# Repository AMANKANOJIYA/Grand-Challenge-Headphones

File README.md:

# Grand-Challenge-Headphones
The main objective of this grand challenge was to energize young minds and develop indigenous innovative commercially viable 
product designs which can be up- scaled further under a Centre of Excellence being setup by Centre for Development of Advanced 
Computing (CDAC).
# P-007: To design a low-cost Bluetooth or a USB headset
A headset is a device that provides a two-way connection to the user's cell phone via Bluetooth.
Expected features are touch control, noise cancellation, low battery consumption.

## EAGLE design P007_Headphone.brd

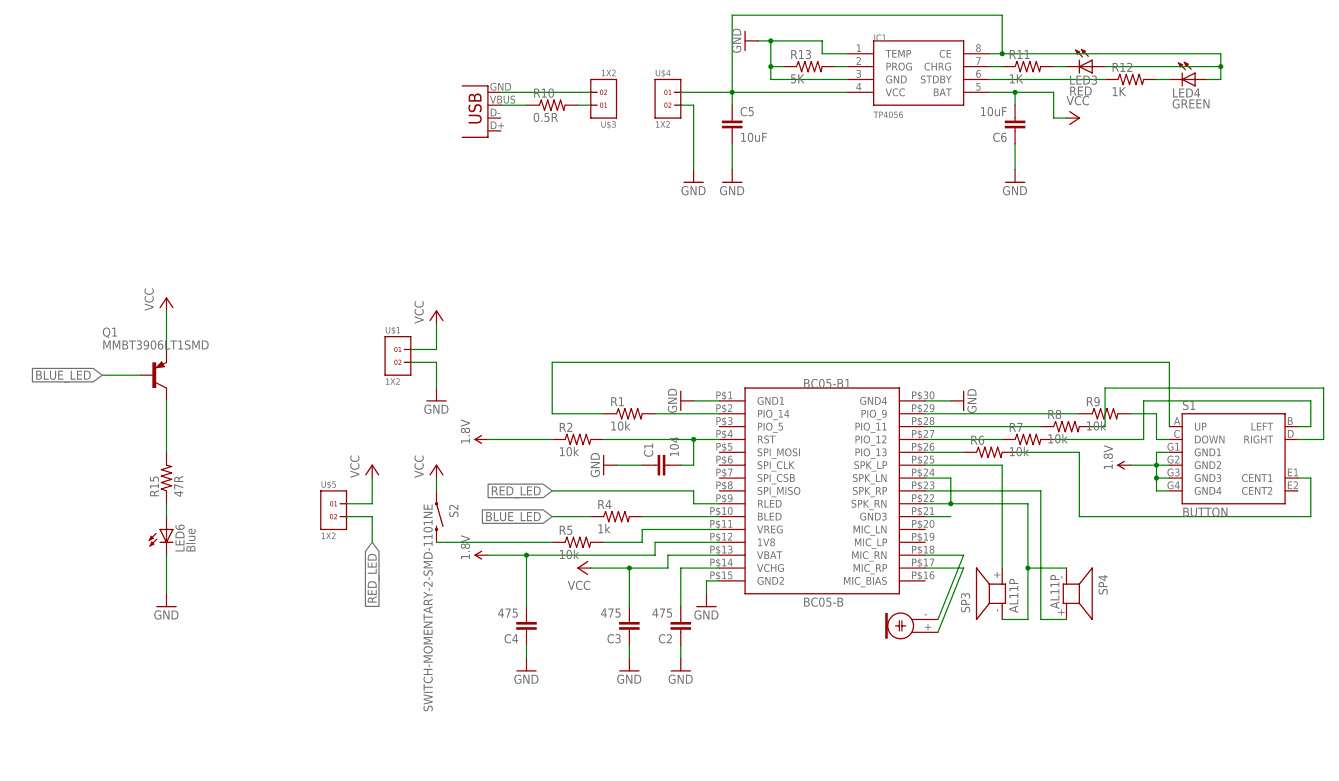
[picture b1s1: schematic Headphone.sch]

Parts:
BC05-B1: BC05-B
C1: 104; C0603K
C2, C3, C4: 475; C0603K
C5, C6: 10uF; C0805K
IC1: TP4056; SOP-8
LED3: RED; CHIP-LED0805
LED4: GREEN; CHIP-LED0805
LED6: Blue; CHIP-LED0805
M1: ELECTRET_MICROPHON-TOM-1545P-R; TOM-1545P-R
Q1: MMBT3906LT1SMD; SOT23-BEC
R1, R2, R5, R6, R7, R8, R9: 10k; R0603
R4: 1k; R0603
R10: 0.5R; M0805
R11, R12: 1K; R0603
R13: 5K; R0603
R15: 47R; R0603
S1: BUTTON
S2: SWITCH-MOMENTARY-2-SMD-1101NE; TACTILE-SWITCH-1101NE
SP3, SP4: AL11P
U$1, U$3, U$4, U$5: 1X2
X1: USB-MICROB

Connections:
1.8V: BC05-B1.P$12 (1V8), C4.2, R2.1, S1.G1 (GND1), S1.G2 (GND2), S1.G3 (GND3), S1.G4 (GND4)
BLUE_LED: Q1.B, R4.1
GND: BC05-B1.P$1 (GND1), BC05-B1.P$15 (GND2), BC05-B1.P$30 (GND4), C1.1, C2.1, C3.1, C4.1, C5.2, C6.1, IC1.1 (TEMP), IC1.3 (GND), LED6.C, R13.1, U$1.2, U$4.2
unnamed: BC05-B1.P$2 (PIO_14), R1.2
unnamed: BC05-B1.P$4 (RST), C1.2, R2.2
unnamed: BC05-B1.P$11 (VREG), R5.2
unnamed: BC05-B1.P$10 (BLED), R4.2
unnamed: BC05-B1.P$17 (MIC_RP), M1.+ (1)
unnamed: BC05-B1.P$18 (MIC_RN), M1.- (2)
unnamed: BC05-B1.P$25 (SPK_LP), SP3.+ (2)
unnamed: BC05-B1.P$29 (PIO_9), R9.1
unnamed: BC05-B1.P$28 (PIO_11), R8.1
unnamed: BC05-B1.P$27 (PIO_12), R7.1
unnamed: BC05-B1.P$26 (PIO_13), R6.1
unnamed: R7.2, S1.B (LEFT)
unnamed: R8.2, S1.D (RIGHT)
unnamed: R6.2, S1.E1 (CENT1)
unnamed: R10.2, U$3.1
unnamed: R1.1, S1.A (UP)
unnamed: R5.1, S2.P$2 (2)
unnamed: BC05-B1.P$23 (SPK_RP), SP4.+ (2)
unnamed: BC05-B1.P$14 (VCHG), C2.2
unnamed: BC05-B1.P$22 (SPK_RN), BC05-B1.P$24 (SPK_LN), SP3.- (1), SP4.- (1)
unnamed: R10.1, X1.VBUS
unnamed: C5.1, IC1.4 (VCC), IC1.8 (CE), LED3.A, LED4.A, U$4.1
unnamed: IC1.7 (CHRG), R11.1
unnamed: LED3.C, R11.2
unnamed: LED4.C, R12.2
unnamed: IC1.6 (STDBY), R12.1
unnamed: IC1.2 (PROG), R13.2
unnamed: LED6.A, R15.1
unnamed: R9.2, S1.C (DOWN)
unnamed: U$3.2, X1.GND
unnamed: Q1.C, R15.2
RED_LED: BC05-B1.P$9 (RLED), U$5.2
VCC: BC05-B1.P$13 (VBAT), C3.2, C6.2, IC1.5 (BAT), Q1.E, S2.P$1 (1), U$1.1, U$5.1

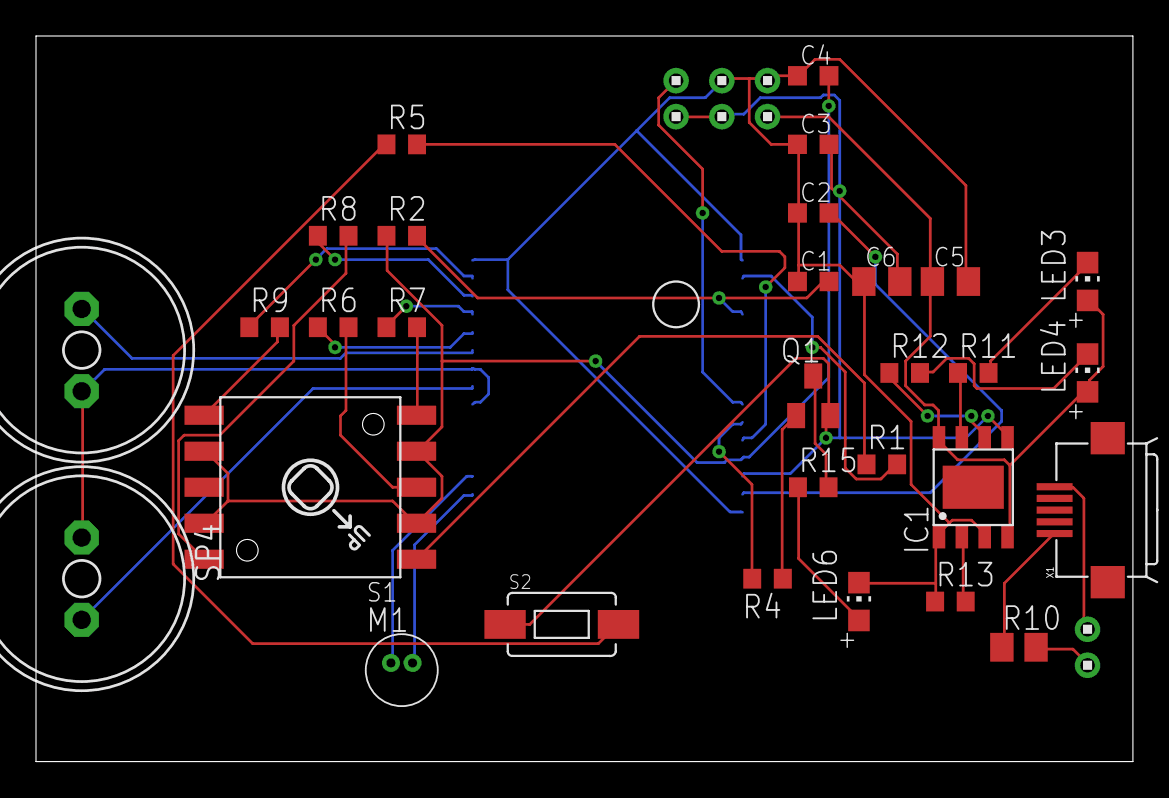
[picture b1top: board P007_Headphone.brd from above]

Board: 2 copper layers, 60.9 x 40.3 mm, 35 parts (0 on the bottom side), 36 nets.

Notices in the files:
parts and their libraries:
SparkFun-Electromechanical: Licensing: CC v3.0 Share-Alike You are welcome to use this library for commercial purposes.
